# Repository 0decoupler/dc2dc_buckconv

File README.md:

challenge :::

Select and layout a synchronous DC-DC buck converter. 
Input: 12 V; 
Output: 5 V
and up to 3 A

here, i track it.

3D View:

PCB Layout:

some problems i noticed with my design:
- [ ] as the datasheet's layout example seems to target 2+ layer boards, i just opted for regular traces with the vias instead of the SW copper pour in the internal layer. cant really know if it causes issues. should not in theory
- [ ] having issues with 3D models loading
- [ ] GND and VIN copper zones are quite close to each other. Does it cause noise issues? Should not, huh, as GND is not a signal traces?
- [ ] Traces and via parameters should be good for high current spikes. Wanna see how it performs on the physical bring-up.
- [x] ...

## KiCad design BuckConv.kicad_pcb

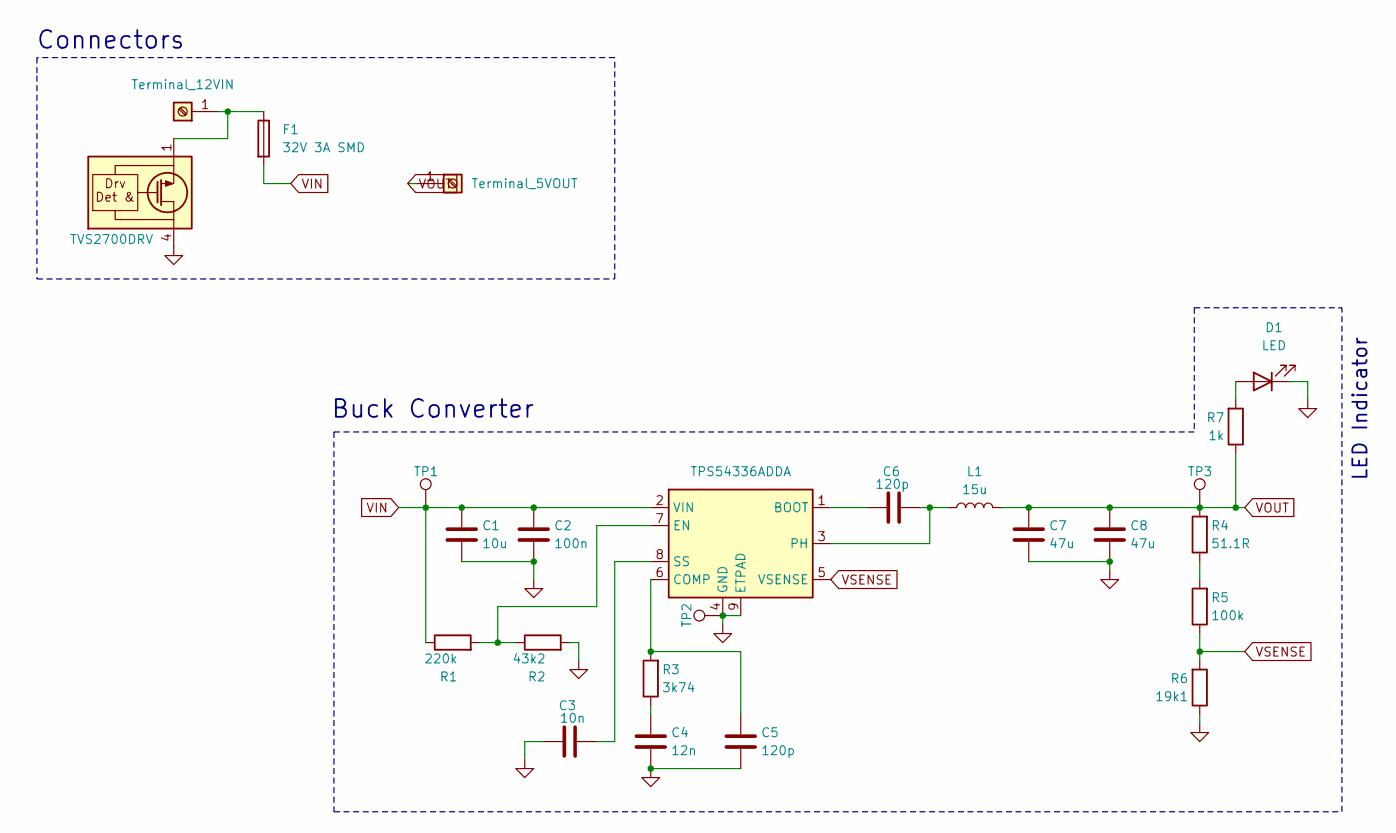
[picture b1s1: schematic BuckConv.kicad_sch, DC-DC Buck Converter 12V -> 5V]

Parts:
Buck1: TPS54336ADDA; TI_SO-PowerPAD-8_ThermalVias
C1: 10u; C_0603_1608Metric
C2: 100n; C_0402_1005Metric
C3: 10n; C_0402_1005Metric
C4: 12n; C_0402_1005Metric
C5, C6: 120p; C_0402_1005Metric
C7, C8: 47u; C_0603_1608Metric
D1: LED; LED_0805_2012Metric
F1: 32V 3A SMD; Fuse_0603_1608Metric
L1: 15u; L_7.3x7.3_H3.5
R1: 220k; R_0402_1005Metric
R2: 43k2; R_0402_1005Metric
R3: 3k74; R_0402_1005Metric
R4: 51.1R; R_0402_1005Metric
R5: 100k; R_0402_1005Metric
R6: 19k1; R_0402_1005Metric
R7: 1k; R_0402_1005Metric
TP1, TP2, TP3: TestPoint; TestPoint_Pad_D1.0mm
TVS1: TVS2700DRV; WSON-6-1EP_2x2mm_P0.65mm_EP1x1.6mm
VIN1: Terminal_12VIN; TerminalBlock_MetzConnect_360271_1x01_Horizontal_ScrewM3.0_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
VOUT1: Terminal_5VOUT; TerminalBlock_MetzConnect_360271_1x01_Horizontal_ScrewM3.0_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

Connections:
GND: Buck1.4 (GND), Buck1.9 (ETPAD), C1.2, C2.2, C3.1, C4.2, C5.2, C7.2, C8.2, D1.1 (K), R2.2, R6.1, TP2.1 (1_1), TVS1.4 (IN), TVS1.5 (IN), TVS1.6 (IN)
unnamed: Buck1.1 (BOOT), C6.1
unnamed: Buck1.6 (COMP), C5.1, R3.2
unnamed: Buck1.7 (EN), R1.2, R2.1
unnamed: Buck1.3 (PH), C6.2, L1.1
unnamed: Buck1.8 (SS), C3.2
unnamed: C4.1, R3.1
unnamed: D1.2 (A), R7.2
unnamed: R4.1, R5.2
unnamed 9: F1.1, TVS1.1 (GND), TVS1.2 (GND), TVS1.3 (GND), TVS1.7 (GND), VIN1.1; also elsewhere on the board
VIN: Buck1.2 (VIN), C1.1, C2.1, F1.2, R1.1, TP1.1 (1_1)
VOUT: C7.1, C8.1, L1.2, R4.2, R7.1, TP3.1 (1_1), VOUT1.1; also elsewhere on the board
VSENSE: Buck1.5 (VSENSE), R5.1, R6.2

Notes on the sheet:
LED Indicator
Buck Converter
Connectors

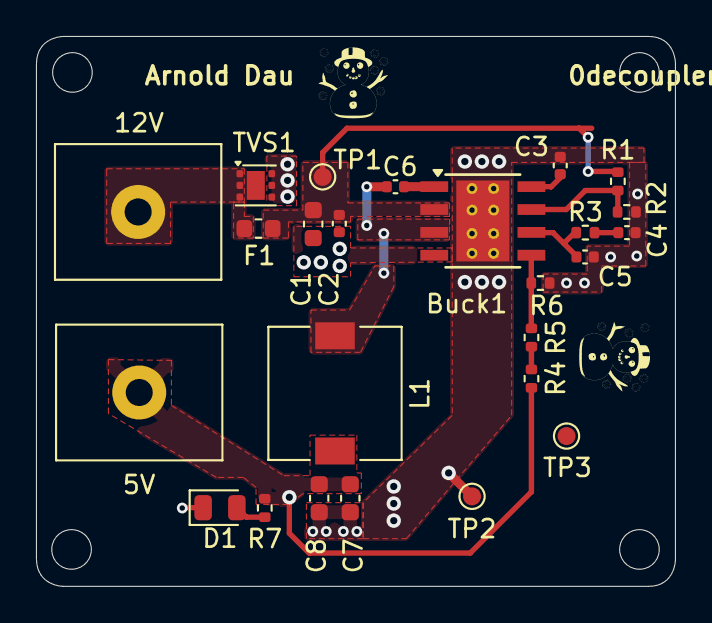
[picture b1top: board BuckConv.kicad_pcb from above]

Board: 2 copper layers, 35.5 x 30.5 mm, 27 parts (0 on the bottom side), 13 nets.

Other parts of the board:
5V: Terminal_5VOUT; TerminalBlock_MetzConnect_360271_1x01_Horizontal_ScrewM3.0_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
12V: Terminal_12VIN; TerminalBlock_MetzConnect_360271_1x01_Horizontal_ScrewM3.0_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
G: LOGO
G#2: LOGO

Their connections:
unnamed 9: 12V.1 (Pin_1_1); also elsewhere on the board
VOUT: 5V.1 (Pin_1_1); also elsewhere on the board
